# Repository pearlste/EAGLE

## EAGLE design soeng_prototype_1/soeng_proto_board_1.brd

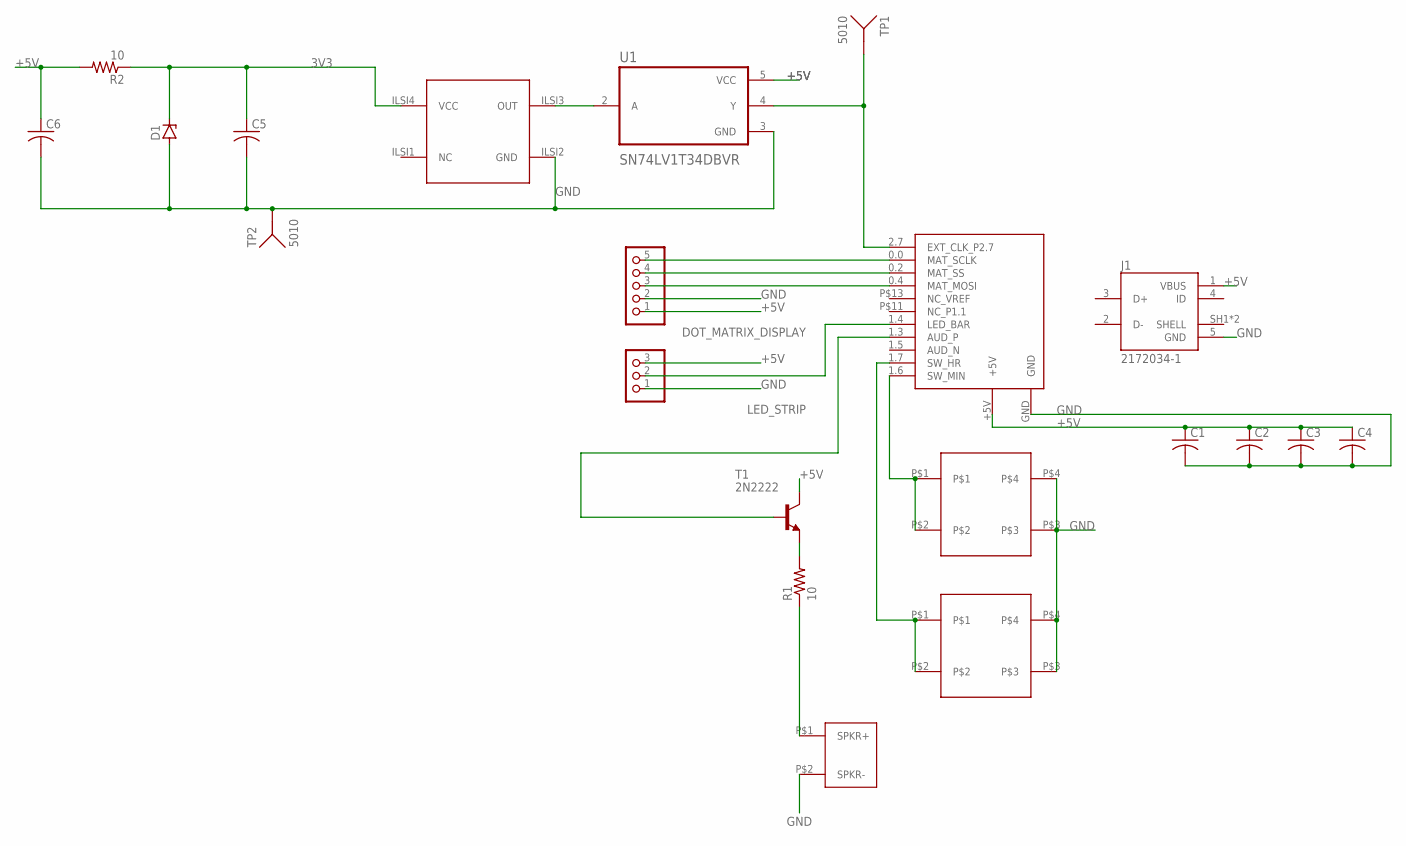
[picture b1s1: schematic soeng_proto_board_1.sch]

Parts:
C1, C2, C3, C4, C5, C6: C-US025-025X050; C025-025X050
D1: ZENER-DIODEZD-10; ZDIO-10
DOT_MATRIX_DISPLAY: PINHD-1X5; 1X05
J1: 2172034-1; TE_2172034-1
LED_STRIP: PINHD-1X3; 1X03
R1, R2: 10; 0207/9
T1: 2N2222; TO92-EBC-OVAL
TP1, TP2: 5010; TP_5010
U1: SN74LV1T34DBVR; SOT95P280X145-5N
U$1: CY8CKIT-149; CY8CKIT-142
U$2, U$3: RDI-PUSHBUTTON
U$4: MICRO_SPKR
U$5: ILSI-I538; ILSI-I538SERIES

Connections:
3V3: C5.1, D1.C, R2.1, U$5.ILSI4 (VCC)
+5V: C1.1, C2.1, C3.1, C4.1, C6.1, DOT_MATRIX_DISPLAY.1, J1.1 (VBUS), LED_STRIP.3, R2.2, T1.C, U1.5 (VCC), U$1.+5V
GND: C1.2, C2.2, C3.2, C4.2, C5.2, C6.2, D1.A, DOT_MATRIX_DISPLAY.2, J1.5 (GND), LED_STRIP.1, TP2.1, U1.3 (GND), U$1.GND, U$2.P$3, U$2.P$4, U$3.P$3, U$3.P$4, U$4.P$2 (SPKR-), U$5.ILSI2 (GND)
unnamed: DOT_MATRIX_DISPLAY.5, U$1.0.0 (MAT_SCLK)
unnamed: DOT_MATRIX_DISPLAY.4, U$1.0.2 (MAT_SS)
unnamed: DOT_MATRIX_DISPLAY.3, U$1.0.4 (MAT_MOSI)
unnamed: T1.B, U$1.1.3 (AUD_P)
unnamed: LED_STRIP.2, U$1.1.4 (LED_BAR)
unnamed: R1.2, T1.E
unnamed: U$1.1.7 (SW_HR), U$3.P$1, U$3.P$2
unnamed: U$1.1.6 (SW_MIN), U$2.P$1, U$2.P$2
unnamed: R1.1, U$4.P$1 (SPKR+)
unnamed: TP1.1, U1.4 (Y), U$1.2.7 (EXT_CLK_P2.7)
unnamed: U1.2 (A), U$5.ILSI3 (OUT)
SHELL: J1.SH1 (SHELL), J1.SH2 (SHELL)

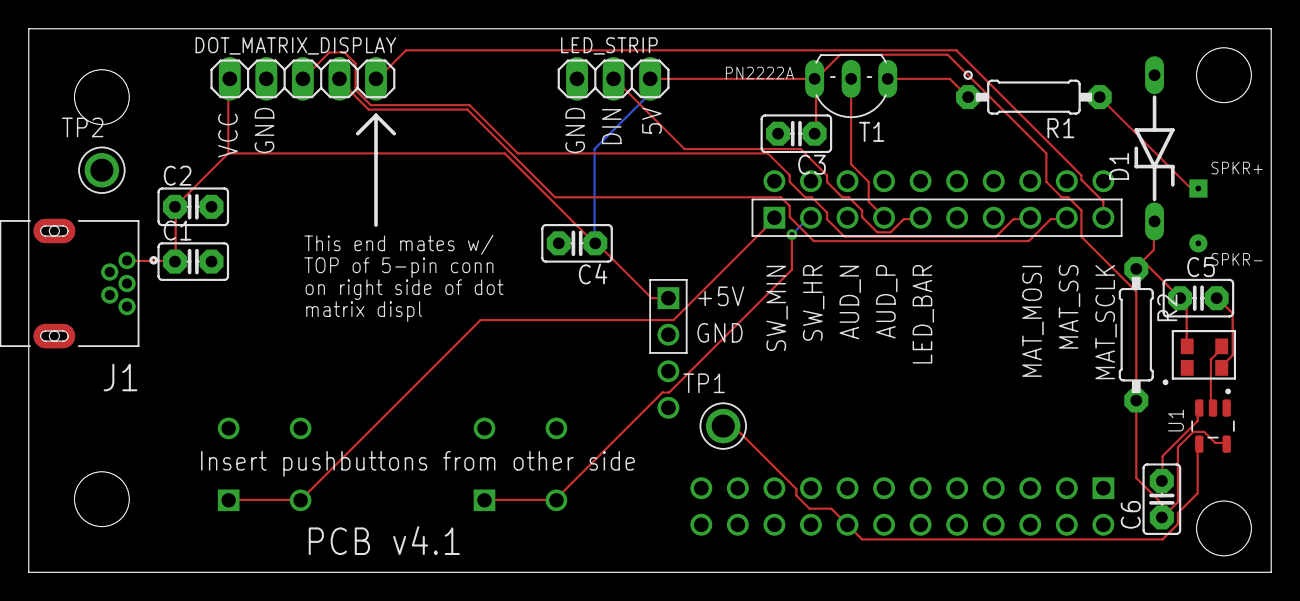
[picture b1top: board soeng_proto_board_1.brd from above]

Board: 2 copper layers, 86.3 x 37.8 mm, 21 parts (0 on the bottom side), 15 nets.

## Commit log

2022-02-12 First time check-in
2022-02-12 Adding eagle.epf
2022-03-14 PCB Rev. 2
2022-03-26 Rev. 3
2022-12-05 Added TCXO, 3.3V Zener, RC
2022-12-29 V4.1 sent out for fab. Changed oscillator, added level shifters
